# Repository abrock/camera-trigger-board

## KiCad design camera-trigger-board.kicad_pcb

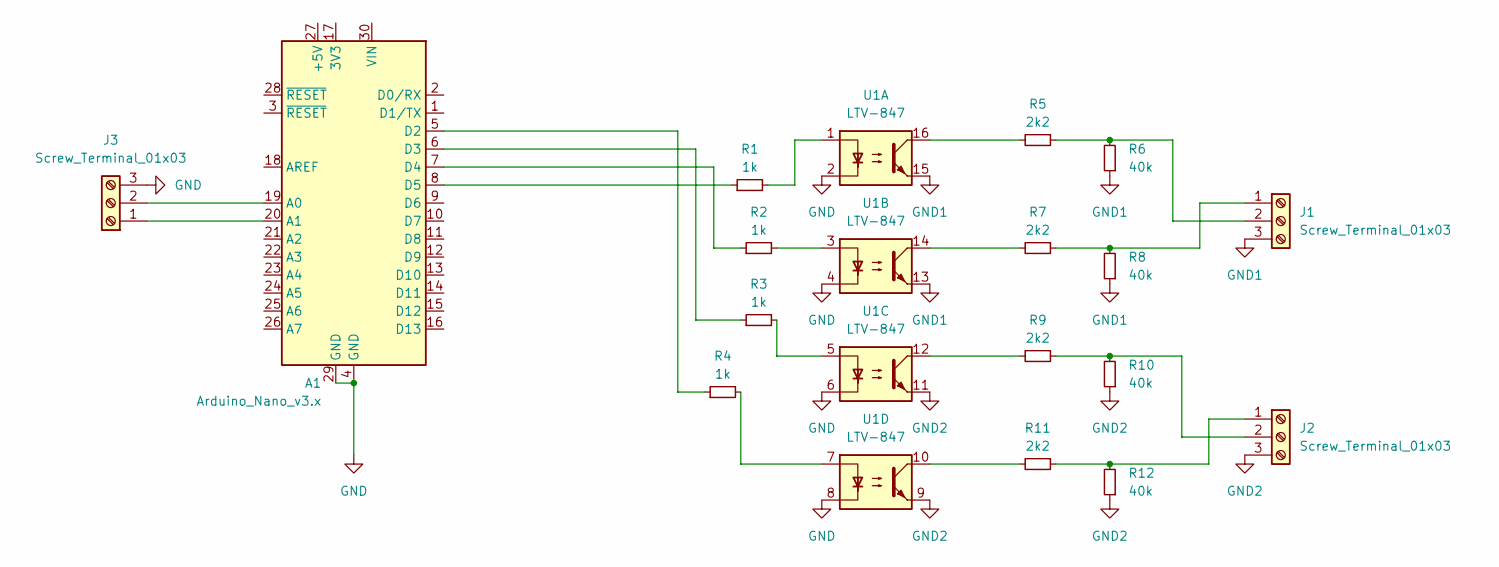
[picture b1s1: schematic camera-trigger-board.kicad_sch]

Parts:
A1: Arduino_Nano_v3.x; Arduino_Nano
J1, J2, J3: Screw_Terminal_01x03; TerminalBlock_bornier-3_P5.08mm
R1, R2, R3, R4: 1k; R_Axial_DIN0204_L3.6mm_D1.6mm_P7.62mm_Horizontal
R5, R7, R9, R11: 2k2; R_Axial_DIN0204_L3.6mm_D1.6mm_P7.62mm_Horizontal
R6, R8, R10, R12: 40k; R_Axial_DIN0204_L3.6mm_D1.6mm_P7.62mm_Horizontal
U1: LTV-847; DIP-16_W7.62mm

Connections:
GND: A1.4 (GND), A1.29 (GND), J3.3, U1.2, U1.4, U1.6, U1.8
GND1: J1.3, R6.1, R8.1, U1.13, U1.15
GND2: J2.3, R10.1, R12.1, U1.9, U1.11
unnamed: A1.19 (A0), J3.2
unnamed: A1.20 (A1), J3.1
unnamed: A1.5 (D2), R4.1
unnamed: A1.6 (D3), R3.1
unnamed: A1.7 (D4), R2.1
unnamed: A1.8 (D5), R1.1
unnamed: J1.1, R7.1, R8.2
unnamed: J1.2, R5.1, R6.2
unnamed: J2.1, R11.1, R12.2
unnamed: J2.2, R9.1, R10.2
unnamed: R1.2, U1.1
unnamed: R2.2, U1.3
unnamed: R3.2, U1.5
unnamed: R4.2, U1.7
unnamed: R5.2, U1.16
unnamed: R7.2, U1.14
unnamed: R9.2, U1.12
unnamed: R11.2, U1.10

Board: 2 copper layers, 17 parts (0 on the bottom side), 21 nets, no tracks yet.

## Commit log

2024-01-02 Initial commit.
